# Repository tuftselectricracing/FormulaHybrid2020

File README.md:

# Formula Hybrid 2020
Files and such for Formula Hybrid 2020

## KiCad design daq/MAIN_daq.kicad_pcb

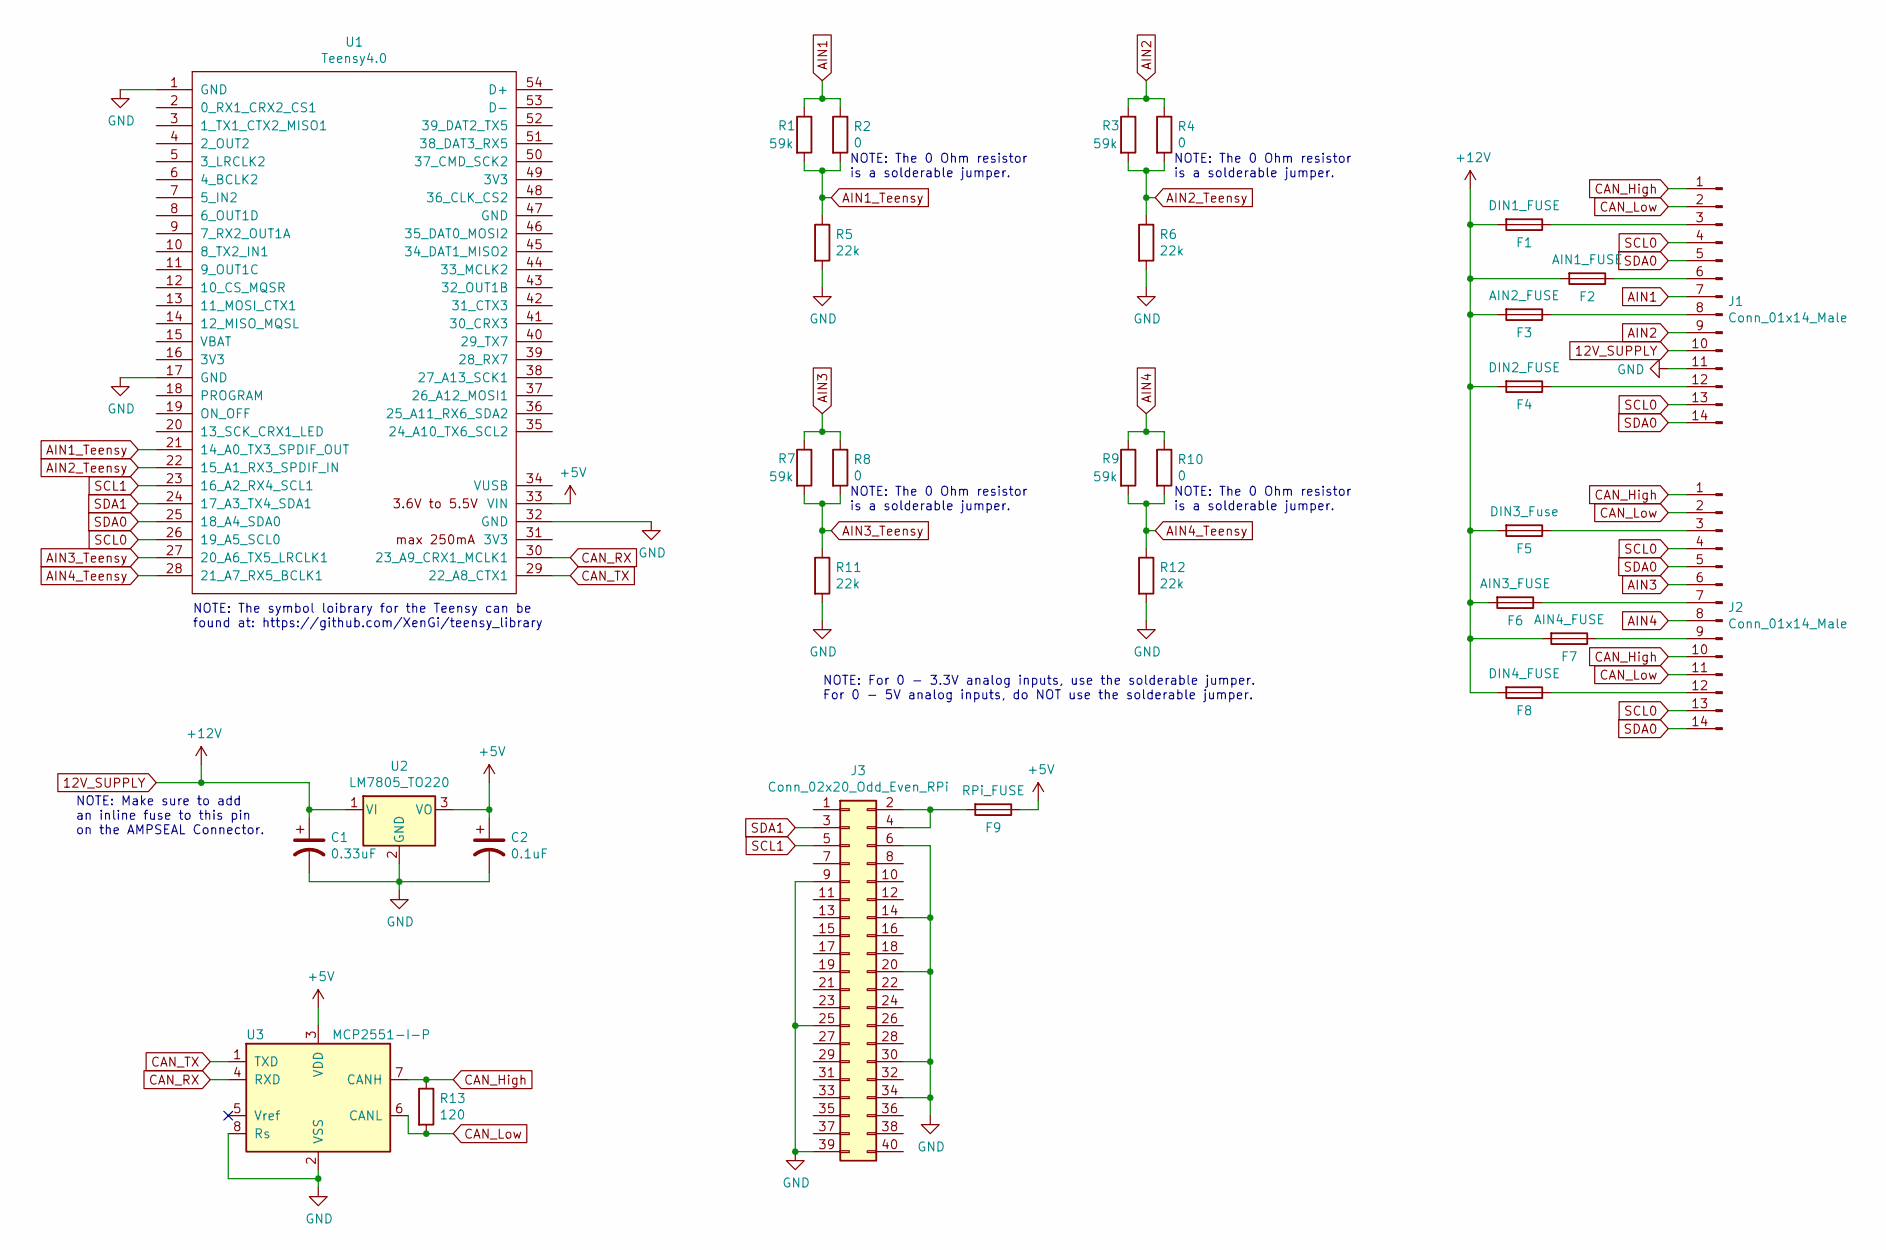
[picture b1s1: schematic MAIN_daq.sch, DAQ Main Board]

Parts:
C1: 0.33uF; C_0603_1608Metric_Pad1.08x0.95mm_HandSolder
C2: 0.1uF; C_0402_1005Metric_Pad0.74x0.62mm_HandSolder
F1: DIN1_FUSE; Fuseholder_Blade_Mini_Keystone_3568
F2: AIN1_FUSE; Fuseholder_Blade_Mini_Keystone_3568
F3: AIN2_FUSE; Fuseholder_Blade_Mini_Keystone_3568
F4: DIN2_FUSE; Fuseholder_Blade_Mini_Keystone_3568
F5: DIN3_Fuse; Fuseholder_Blade_Mini_Keystone_3568
F6: AIN3_FUSE; Fuseholder_Blade_Mini_Keystone_3568
F7: AIN4_FUSE; Fuseholder_Blade_Mini_Keystone_3568
F8: DIN4_FUSE; Fuseholder_Blade_Mini_Keystone_3568
F9: RPi_FUSE; Fuseholder_Blade_Mini_Keystone_3568
J1, J2: Conn_01x14_Male; TE_776266-1
J3: Conn_02x20_Odd_Even_RPi; PinHeader_2x20_P2.54mm_Vertical
R1, R3, R7, R9: 59k; R_0603_1608Metric_Pad0.98x0.95mm_HandSolder
R2, R4, R8, R10: 0; SolderJumper-2_P1.3mm_Open_TrianglePad1.0x1.5mm
R5, R6, R11, R12: 22k; R_0603_1608Metric_Pad0.98x0.95mm_HandSolder
R13: 120; R_0603_1608Metric_Pad0.98x0.95mm_HandSolder
U1: Teensy4.0; Teensy40
U2: LM7805_TO220; TO-220-3_Horizontal_TabDown
U3: MCP2551-I-P; DIP-8_W7.62mm

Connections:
12V_SUPPLY: C1.1, F1.2, F2.2, F3.2, F4.2, F5.2, F6.2, F7.2, F8.2, J1.10, U2.1 (VI)
+5V: C2.1, F9.1, U1.33 (VIN), U2.3 (VO), U3.3 (VDD)
AIN1: J1.7, R1.1, R2.1
AIN1_Teensy: R1.2, R2.2, R5.1, U1.21 (14_A0_TX3_SPDIF_OUT)
AIN2: J1.9, R3.1, R4.1
AIN2_Teensy: R3.2, R4.2, R6.1, U1.22 (15_A1_RX3_SPDIF_IN)
AIN3: J2.6, R7.1, R8.1
AIN3_Teensy: R7.2, R8.2, R11.1, U1.27 (20_A6_TX5_LRCLK1)
AIN4: J2.8, R9.1, R10.1
AIN4_Teensy: R9.2, R10.2, R12.1, U1.28 (21_A7_RX5_BCLK1)
CAN_High: J1.1, J2.1, J2.10, R13.1, U3.7 (CANH)
CAN_Low: J1.2, J2.2, J2.11, R13.2, U3.6 (CANL)
CAN_RX: U1.30 (23_A9_CRX1_MCLK1), U3.4 (RXD)
CAN_TX: U1.29 (22_A8_CTX1), U3.1 (TXD)
GND: C1.2, C2.2, J1.11, J3.6, J3.9, J3.14, J3.20, J3.25, J3.30, J3.34, J3.39, R5.2, R6.2, R11.2, R12.2, U1.1 (GND), U1.17 (GND), U1.32 (GND), U2.2 (GND), U3.2 (VSS), U3.8 (Rs)
unnamed: F1.1, J1.3
unnamed: F2.1, J1.6
unnamed: F3.1, J1.8
unnamed: F4.1, J1.12
unnamed: F5.1, J2.3
unnamed: F6.1, J2.7
unnamed: F7.1, J2.9
unnamed: F8.1, J2.12
unnamed: F9.2, J3.2, J3.4
SCL0: J1.4, J1.13, J2.4, J2.13, U1.26 (19_A5_SCL0)
SCL1: J3.5, U1.23 (16_A2_RX4_SCL1)
SDA0: J1.5, J1.14, J2.5, J2.14, U1.25 (18_A4_SDA0)
SDA1: J3.3, U1.24 (17_A3_TX4_SDA1)

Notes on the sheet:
NOTE: The symbol loibrary for the Teensy can be found at: https://github.com/XenGi/teensy_library
NOTE: The 0 Ohm resistor is a solderable jumper.
NOTE: Make sure to add an inline fuse to this pin on the AMPSEAL Connector.
NOTE: For 0 - 3.3V analog inputs, use the solderable jumper. For 0 - 5V analog inputs, do NOT use the solderable jumper.

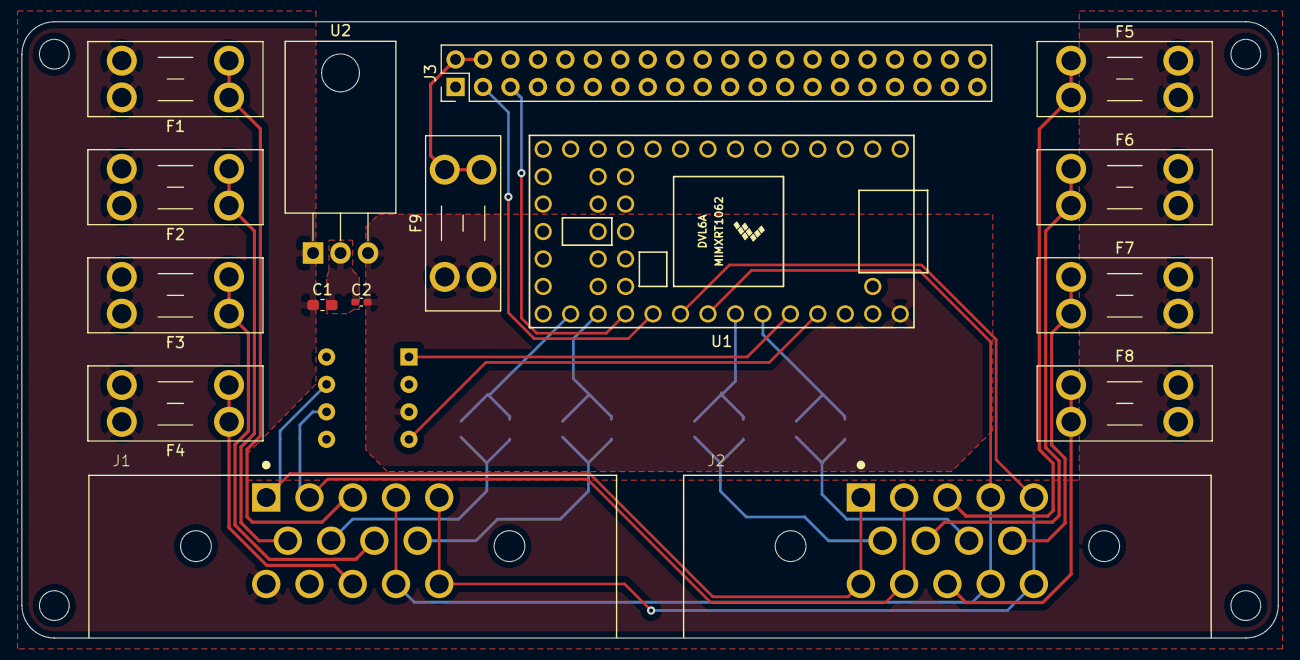
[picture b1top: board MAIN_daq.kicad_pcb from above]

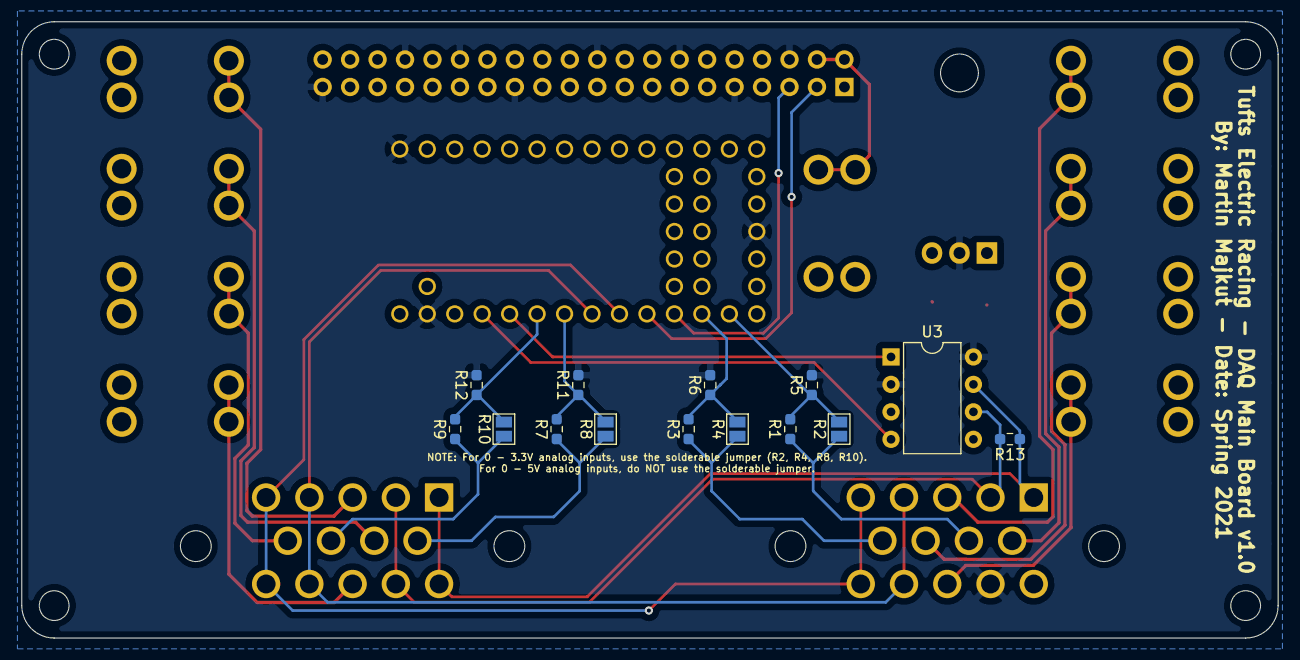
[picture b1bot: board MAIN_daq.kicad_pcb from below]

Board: 2 copper layers, 116.2 x 57.0 mm, 30 parts (14 on the bottom side), 28 nets.

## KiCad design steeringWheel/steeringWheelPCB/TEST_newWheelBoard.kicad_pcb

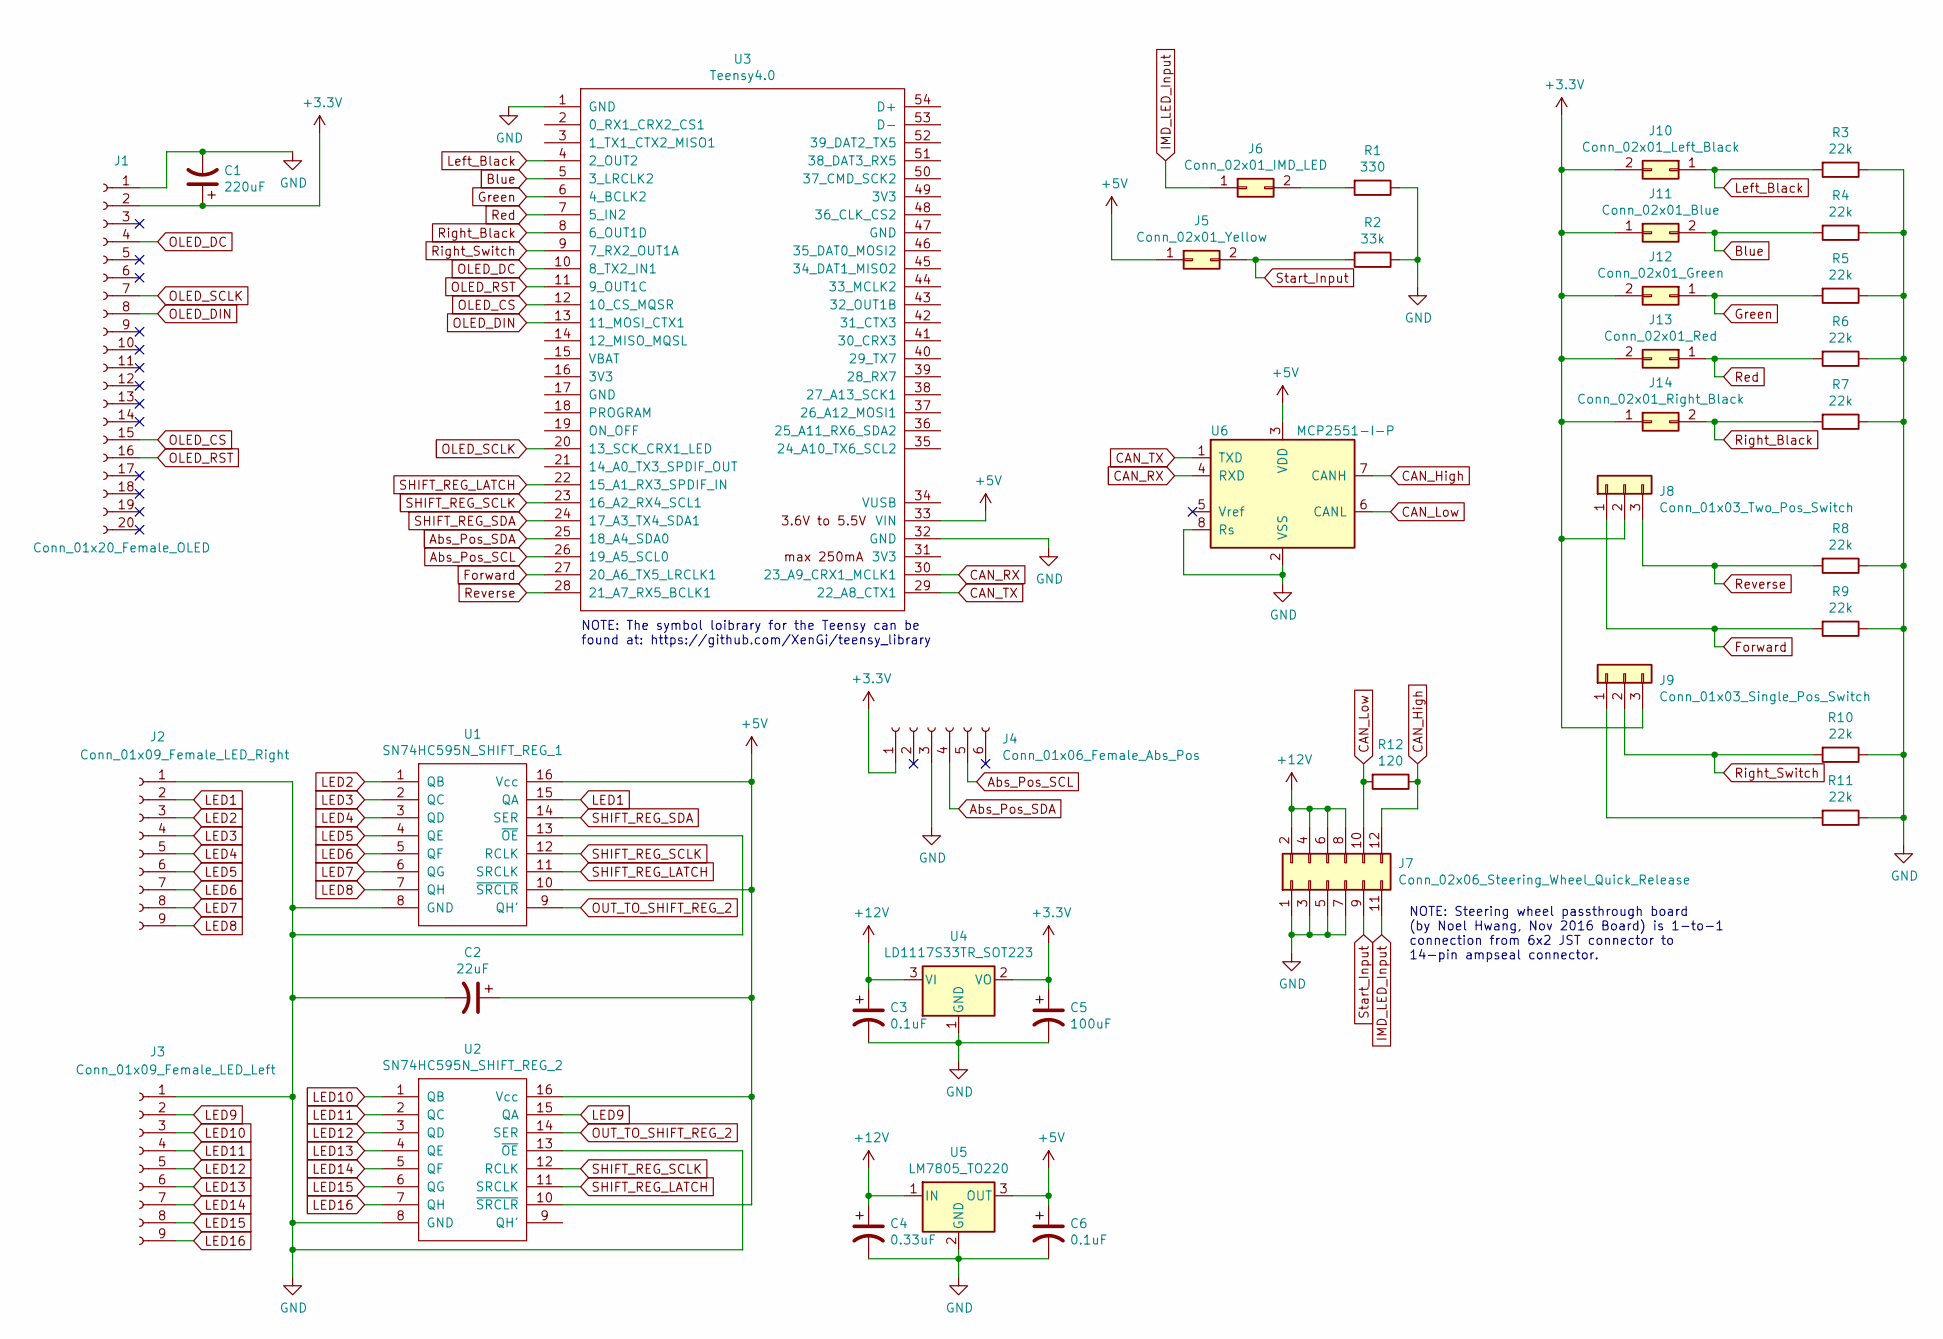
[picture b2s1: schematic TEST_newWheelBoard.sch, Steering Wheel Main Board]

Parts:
C1: 220uF; CP_Radial_D5.0mm_P2.00mm
C2: 22uF; CP_Radial_D4.0mm_P1.50mm
C3, C6: 0.1uF; C_0402_1005Metric
C4: 0.33uF; C_0603_1608Metric_Pad1.05x0.95mm_HandSolder
C5: 100uF; C_1206_3216Metric_Pad1.42x1.75mm_HandSolder
J1: Conn_01x20_Female_OLED; PinHeader_1x20_P2.54mm_Vertical
J2: Conn_01x09_Female_LED_Right; JST_PH_B9B-PH-K_1x09_P2.00mm_Vertical
J3: Conn_01x09_Female_LED_Left; JST_PH_B9B-PH-K_1x09_P2.00mm_Vertical
J4: Conn_01x06_Female_Abs_Pos; PinHeader_1x06_P2.54mm_Vertical
J5: Conn_02x01_Yellow; JST_PH_B2B-PH-K_1x02_P2.00mm_Vertical
J6: Conn_02x01_IMD_LED; JST_PH_B2B-PH-K_1x02_P2.00mm_Vertical
J7: Conn_02x06_Steering_Wheel_Quick_Release; JST_PHD_S12B-PHDSS_2x06_P2.00mm_Horizontal
J8: Conn_01x03_Two_Pos_Switch; JST_PH_B3B-PH-K_1x03_P2.00mm_Vertical
J9: Conn_01x03_Single_Pos_Switch; JST_PH_B3B-PH-K_1x03_P2.00mm_Vertical
J10: Conn_02x01_Left_Black; JST_PH_B2B-PH-K_1x02_P2.00mm_Vertical
J11: Conn_02x01_Blue; JST_PH_B2B-PH-K_1x02_P2.00mm_Vertical
J12: Conn_02x01_Green; JST_PH_B2B-PH-K_1x02_P2.00mm_Vertical
J13: Conn_02x01_Red; JST_PH_B2B-PH-K_1x02_P2.00mm_Vertical
J14: Conn_02x01_Right_Black; JST_PH_B2B-PH-K_1x02_P2.00mm_Vertical
R1: 330; R_0402_1005Metric
R2: 33k; R_0603_1608Metric_Pad1.05x0.95mm_HandSolder
R3, R4, R5, R6, R7, R8, R9, R10, R11: 22k; R_0603_1608Metric_Pad1.05x0.95mm_HandSolder
R12: 120; R_0603_1608Metric_Pad1.05x0.95mm_HandSolder
U1: SN74HC595N_SHIFT_REG_1; DIP-16_W7.62mm_Socket
U2: SN74HC595N_SHIFT_REG_2; DIP-16_W7.62mm_Socket
U3: Teensy4.0; Teensy40
U4: LD1117S33TR_SOT223; TO-220-3_Horizontal_TabDown
U5: LM7805_TO220; TO-220-3_Horizontal_TabDown
U6: MCP2551-I-P; DIP-8_W7.62mm

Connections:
+3V3: C1.1, C5.1, J1.2, J4.1, J8.2, J9.3, J10.2, J11.1, J12.2, J13.2, J14.1, U4.2 (VO)
+5V: C2.1, C6.1, J5.1, U1.10 (~SRCLR), U1.16 (Vcc), U2.10 (~SRCLR), U2.16 (Vcc), U3.33 (VIN), U5.3 (OUT), U6.3 (VDD)
+12V: C3.1, C4.1, J7.2, J7.4, J7.6, J7.8, U4.3 (VI), U5.1 (IN)
Abs_Pos_SCL: J4.5, U3.26 (19_A5_SCL0)
Abs_Pos_SDA: J4.4, U3.25 (18_A4_SDA0)
Blue: J11.2, R4.2, U3.5 (3_LRCLK2)
CAN_High: J7.12, R12.1, U6.7 (CANH)
CAN_Low: J7.10, R12.2, U6.6 (CANL)
CAN_RX: U3.30 (23_A9_CRX1_MCLK1), U6.4 (RXD)
CAN_TX: U3.29 (22_A8_CTX1), U6.1 (TXD)
Forward: J8.1, R9.2, U3.27 (20_A6_TX5_LRCLK1)
GND: C1.2, C2.2, C3.2, C4.2, C5.2, C6.2, J1.1, J2.1, J3.1, J4.3, J7.1, J7.3, J7.5, J7.7, R1.1, R2.1, R3.1, R4.1, R5.1, R6.1, R7.1, R8.1, R9.1, R10.1, R11.1, U1.8 (GND), U1.13 (~OE), U2.8 (GND), U2.13 (~OE), U3.1 (GND), U3.32 (GND), U4.1 (GND), U5.2 (GND), U6.2 (VSS), U6.8 (Rs)
Green: J12.1, R5.2, U3.6 (4_BCLK2)
IMD_LED_Input: J6.1, J7.11
LED1: J2.2, U1.15 (QA)
LED2: J2.3, U1.1 (QB)
LED3: J2.4, U1.2 (QC)
LED4: J2.5, U1.3 (QD)
LED5: J2.6, U1.4 (QE)
LED6: J2.7, U1.5 (QF)
LED7: J2.8, U1.6 (QG)
LED8: J2.9, U1.7 (QH)
LED9: J3.2, U2.15 (QA)
LED10: J3.3, U2.1 (QB)
LED11: J3.4, U2.2 (QC)
LED12: J3.5, U2.3 (QD)
LED13: J3.6, U2.4 (QE)
LED14: J3.7, U2.5 (QF)
LED15: J3.8, U2.6 (QG)
LED16: J3.9, U2.7 (QH)
Left_Black: J10.1, R3.2, U3.4 (2_OUT2)
unnamed: J6.2, R1.2
unnamed: J9.1, R11.2
OLED_CS: J1.15, U3.12 (10_CS_MQSR)
OLED_DC: J1.4, U3.10 (8_TX2_IN1)
OLED_DIN: J1.8, U3.13 (11_MOSI_CTX1)
OLED_RST: J1.16, U3.11 (9_OUT1C)
OLED_SCLK: J1.7, U3.20 (13_SCK_CRX1_LED)
OUT_TO_SHIFT_REG_2: U1.9 (QH'), U2.14 (SER)
Red: J13.1, R6.2, U3.7 (5_IN2)
Reverse: J8.3, R8.2, U3.28 (21_A7_RX5_BCLK1)
Right_Black: J14.2, R7.2, U3.8 (6_OUT1D)
Right_Switch: J9.2, R10.2, U3.9 (7_RX2_OUT1A)
SHIFT_REG_LATCH: U1.11 (SRCLK), U2.11 (SRCLK), U3.22 (15_A1_RX3_SPDIF_IN)
SHIFT_REG_SCLK: U1.12 (RCLK), U2.12 (RCLK), U3.23 (16_A2_RX4_SCL1)
SHIFT_REG_SDA: U1.14 (SER), U3.24 (17_A3_TX4_SDA1)
Start_Input: J5.2, J7.9, R2.2

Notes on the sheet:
NOTE: Steering wheel passthrough board (by Noel Hwang, Nov 2016 Board) is 1-to-1 connection from 6x2 JST connector to 14-pin ampseal connector.
NOTE: The symbol loibrary for the Teensy can be found at: https://github.com/XenGi/teensy_library

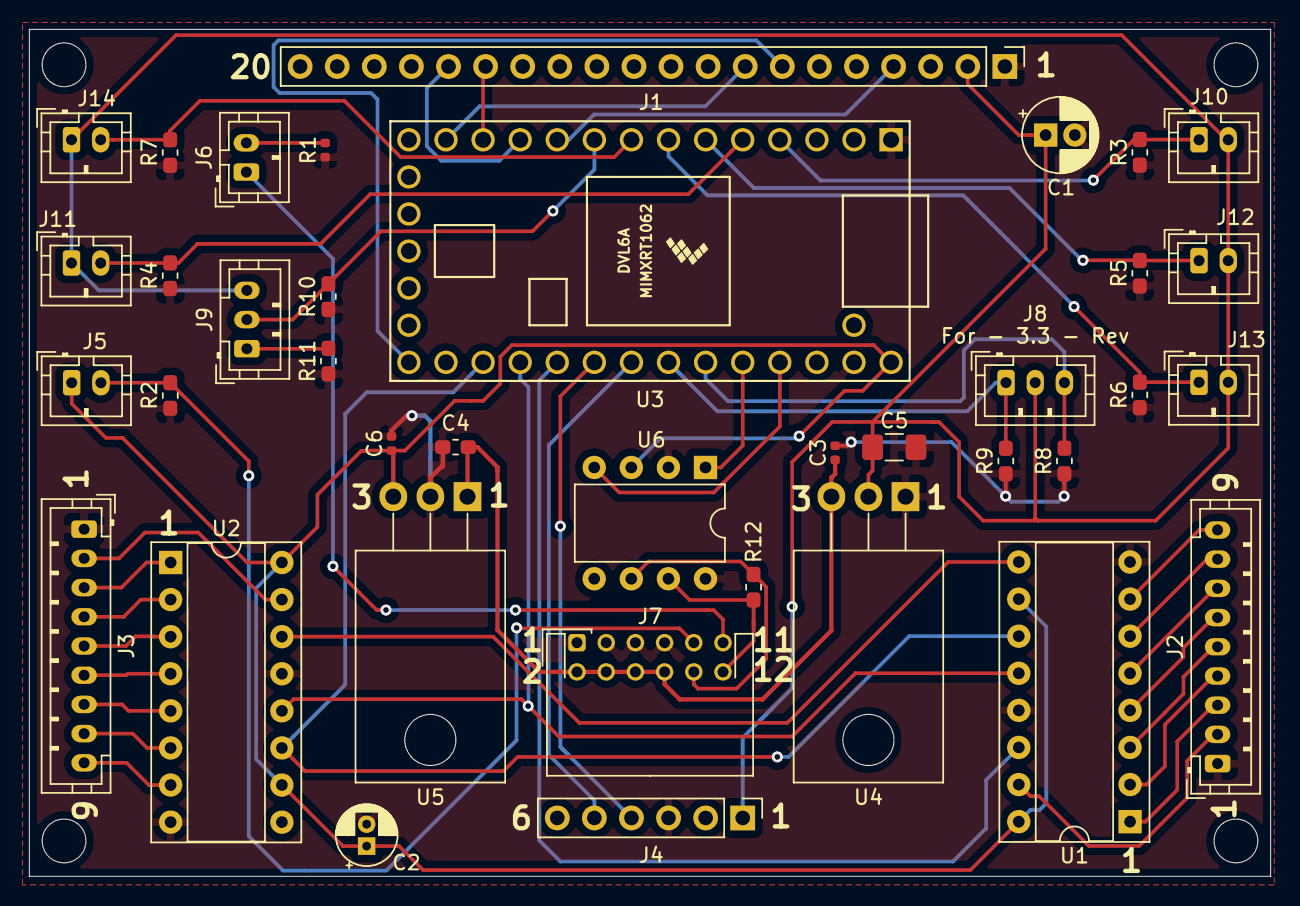
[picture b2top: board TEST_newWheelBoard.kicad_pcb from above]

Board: 2 copper layers, 85.0 x 58.0 mm, 38 parts (0 on the bottom side), 47 nets.

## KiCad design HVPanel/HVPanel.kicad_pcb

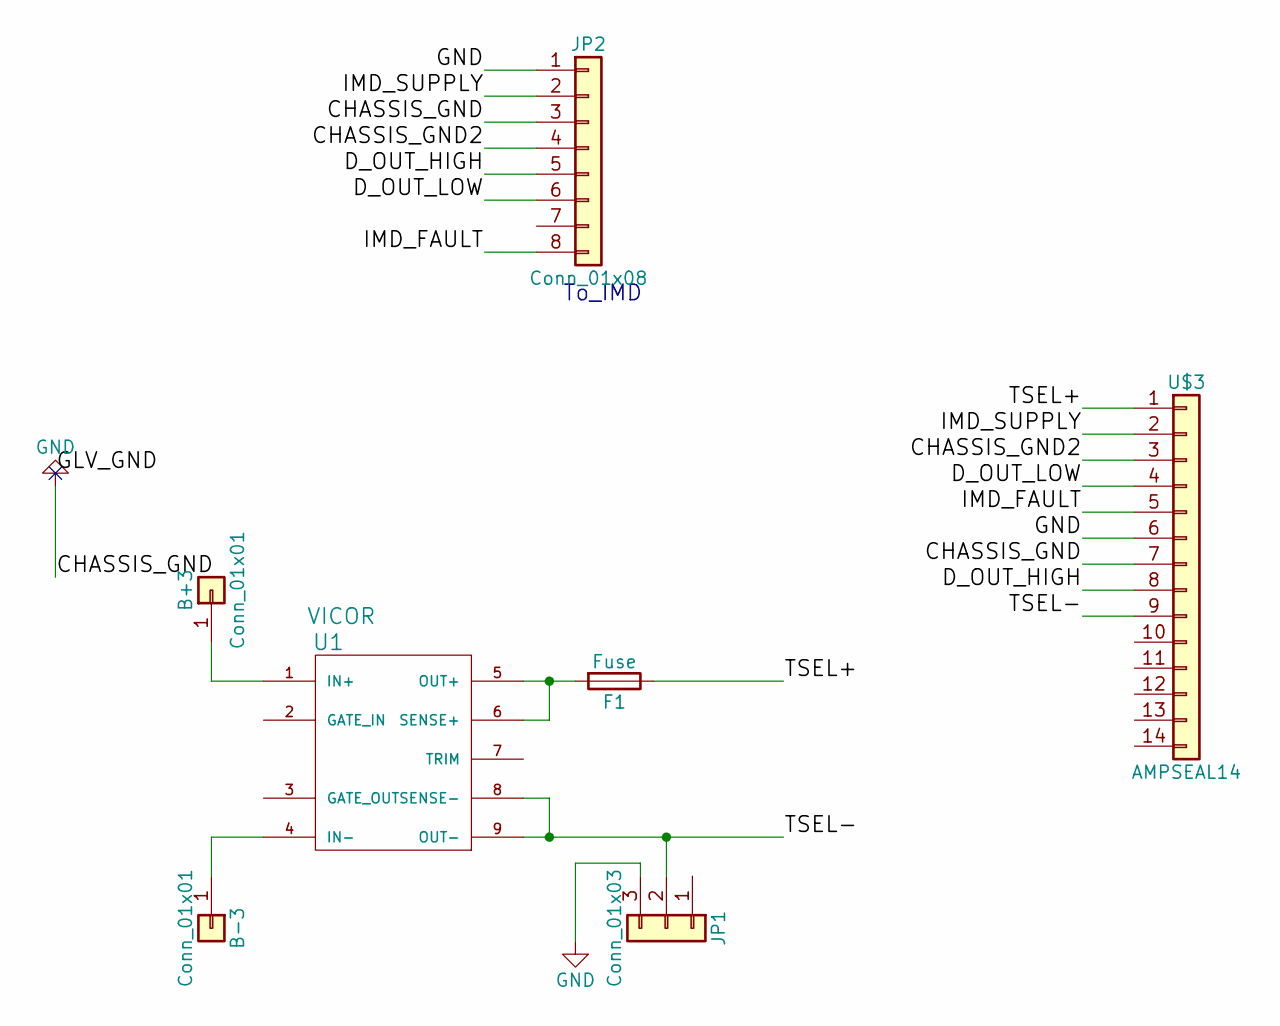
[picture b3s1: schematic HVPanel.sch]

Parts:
B+3: Conn_01x01; SolderWirePad_single_1-5mmDrill
B-3: Conn_01x01; SolderWirePad_single_1-5mmDrill
F1: Fuse; BladeFuse-Mini_Keystone_3568
JP1: Conn_01x03; Pin_Header_Straight_1x03_Pitch2.54mm
JP2: Conn_01x08; Pin_Header_Straight_1x08_Pitch2.54mm
U1: VICOR
U$3: AMPSEAL14; AMP14

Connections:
/CHASSIS_GND2: JP2.4, U$3.3
/D_OUT_HIGH: JP2.5, U$3.8
/D_OUT_LOW: JP2.6, U$3.4
/IMD_FAULT: JP2.8, U$3.5
/IMD_SUPPLY: JP2.2, U$3.2
/TSEL+: F1.1, U$3.1
/TSEL-: JP1.2, U1.8 (SENSE-), U1.9 (OUT-), U$3.9
GND: JP1.3, JP2.1, JP2.3, U$3.6, U$3.7
unnamed: B+3.1, U1.1 (IN+)
unnamed: B-3.1, U1.4 (IN-)
unnamed: F1.2, U1.5 (OUT+), U1.6 (SENSE+)

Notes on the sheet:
To_IMD

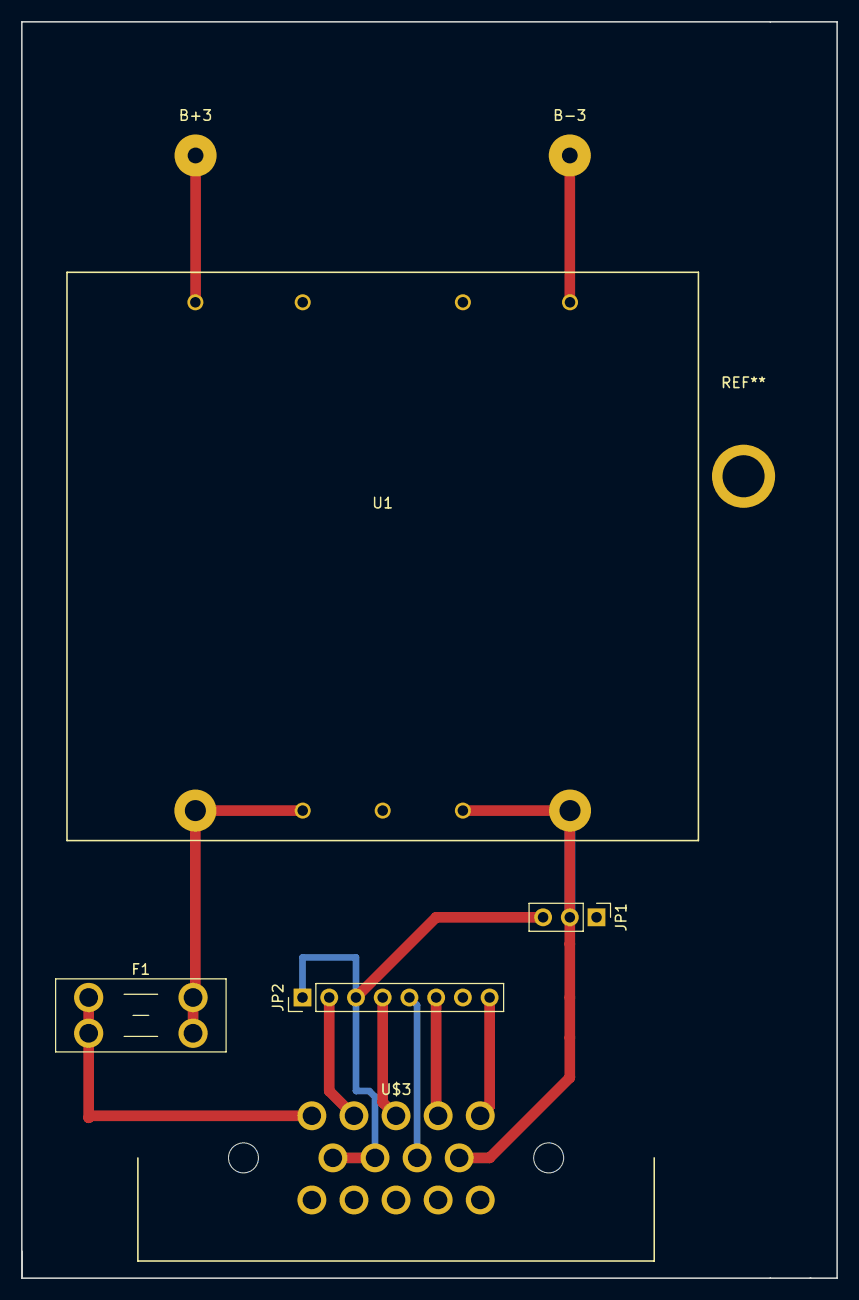
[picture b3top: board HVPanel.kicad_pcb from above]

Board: 2 copper layers, 77.5 x 119.4 mm, 7 parts (0 on the bottom side), 11 nets.

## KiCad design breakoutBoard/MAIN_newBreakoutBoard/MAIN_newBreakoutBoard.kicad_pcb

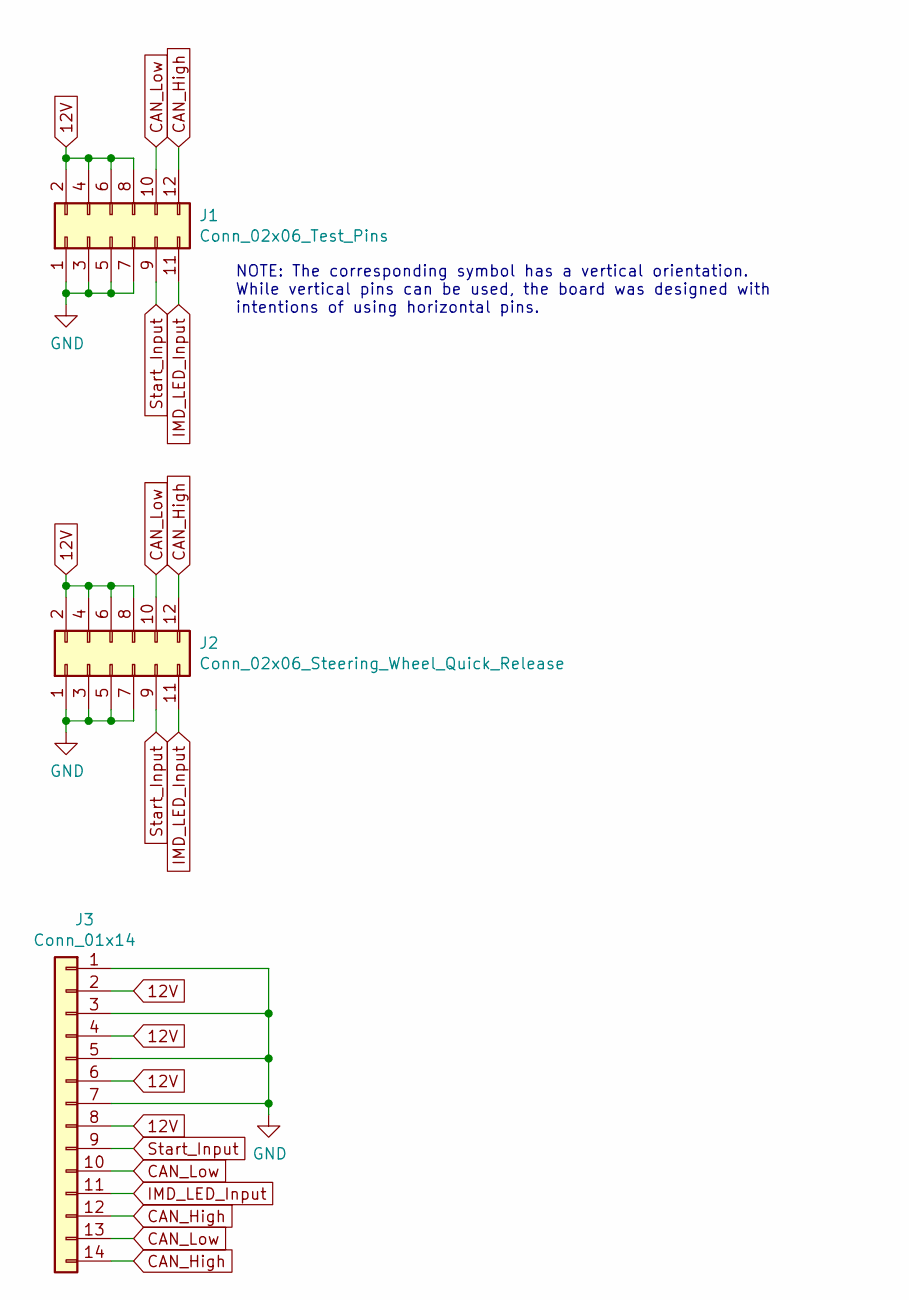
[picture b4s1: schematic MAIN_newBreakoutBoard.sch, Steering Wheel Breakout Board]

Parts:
J1: Conn_02x06_Test_Pins; PinSocket_2x06_P2.54mm_Vertical
J2: Conn_02x06_Steering_Wheel_Quick_Release; JST_PHD_S12B-PHDSS_2x06_P2.00mm_Horizontal
J3: Conn_01x14; TE_776266-1

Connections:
12V: J1.2, J1.4, J1.6, J1.8, J2.2, J2.4, J2.6, J2.8, J3.2, J3.4, J3.6, J3.8
CAN_High: J1.12, J2.12, J3.12, J3.14
CAN_Low: J1.10, J2.10, J3.10, J3.13
GND: J1.1, J1.3, J1.5, J1.7, J2.1, J2.3, J2.5, J2.7, J3.1, J3.3, J3.5, J3.7
IMD_LED_Input: J1.11, J2.11, J3.11
Start_Input: J1.9, J2.9, J3.9

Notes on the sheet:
NOTE: The corresponding symbol has a vertical orientation. While vertical pins can be used, the board was designed with intentions of using horizontal pins.

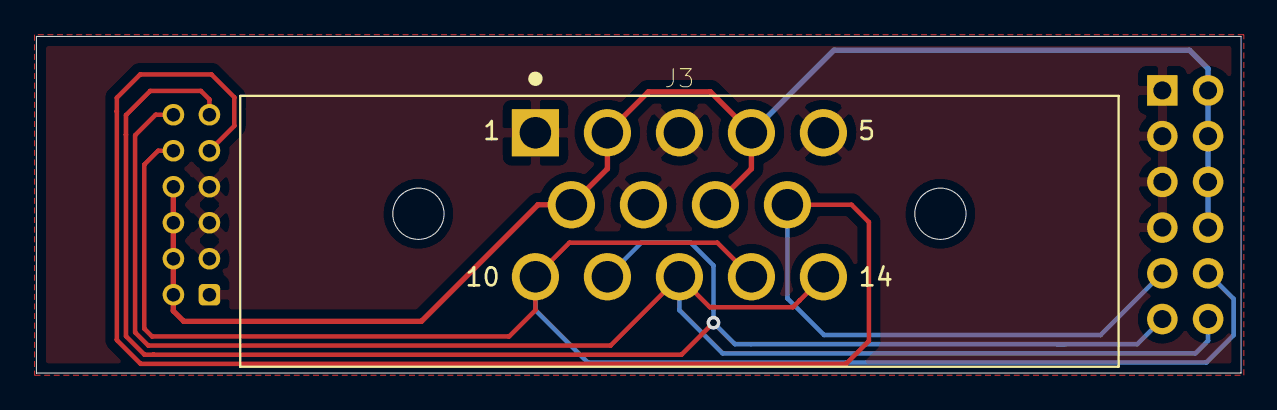
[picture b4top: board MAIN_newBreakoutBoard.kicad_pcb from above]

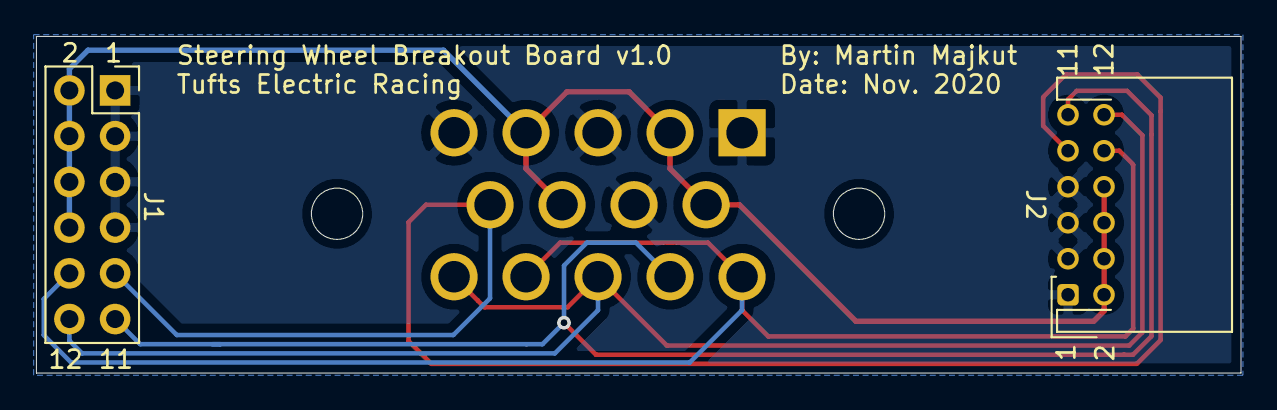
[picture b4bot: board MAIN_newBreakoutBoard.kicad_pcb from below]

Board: 2 copper layers, 66.9 x 18.7 mm, 3 parts (2 on the bottom side), 6 nets.

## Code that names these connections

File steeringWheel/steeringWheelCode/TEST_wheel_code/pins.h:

/*
	pins.h

	This is the supplimentary header file to wheel_code.ino file. It defines
	all the pins used by the Teensy 4.0. The pins are defined as macros to 
	minimize the storage used by the code, thus allowing the board to run
	as quickly as possible. The names used are the same names in the 
	schematic for the board.

	By:   Martin Majkut
			  Tufts Electric Racing
	Date: Aug. 3, 2020
*/

#ifndef PINS_H
#define PINS_H

// Pins for the OLED display (link: https://www.adafruit.com/product/2674)
#define OLED_SCLK 13
#define OLED_DIN 11
#define OLED_CS 10
#define OLED_RST 9
#define OLED_DC 8

// Pins for reading buttons and switches
// (Note: start input button, the yellow button at the time of writing this 
// documentation, bipasses the Teensy and inputs to the motherboard, which 
// why it is not read by the steering wheel)
#define LEFT_BLACK 2
#define BLUE 3
#define GREEN 4
#define RED 5
#define RIGHT_BLACK 6
#define RIGHT_SWITCH 7
#define FORWARD 20
#define REVERSE 21

// Pins for communicating to shift registers thus turning on LEDs
// (link to shift register: https://www.ti.com/store/ti/en/p/product/?p=SN74HC595N)
// NOTE: SCLK and LATCH pins are reversed in schematic (Jan. 2020 Board); will
//       need to be updated in future iterations of board
#define SHIFT_REG_LATCH 16
#define SHIFT_REG_SCLK 15
#define SHIFT_REG_SDA 17

// Pins for absolute position sensor (link: https://www.adafruit.com/product/2472)
#define Abs_Pos_SDA 18
#define Abs_Pos_SCL 19

#endif

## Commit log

2020-08-09 Created folder for steering wheel files
2020-08-09 Created folder for KiCad files
2020-08-09 Created .gitignore before first commit of files
2020-08-09 Added KiCad project
    These files are up to date and are currently the ones being used in the race car's steering wheel as of 8/9/2020.
2020-08-09 Add PCB testing code
2020-08-12 Updated testing code
    Turns out the display wasn't printing what I wanted it to print because I forgot to add in the command that updates the display
2020-08-14 Updated testing code
    The code now responds in real time letting the user know if a button is being read correctly
2020-08-20 Another update to testing code
    Now the code connects to the absolute position sensor and reads position of the steering wheel and displays it on the screen
2020-09-04 LED testing added to testing code + light reformatting
    You know, it becomes really difficult to test something when pins on a board are reversed. Notes added to steering wheel board and code reflect changes that need to implemented for the next iteration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
2020-09-20 CAN bus testing code added
    Code for a swecond Teensy was added to test and verify CAN communication with the steering wheel. The code on the steering wheel was also updated to display CAN messages
2020-11-14 Added breakout board KiCad project
    This is the project for the breakout board that allows the steering wheel to connect to the rest of the race car.
2020-11-15 Slight design updates and gerbers created
    I created gerbers even though OSH Park does not require gerber files.... But whatever, wanted to get some more experience using KiCad :)
2020-11-24 Made use of entire ampseal connector
    Had a late night ah ha momment;; Figured I would make use of all the pins on the ampseal connect and make it so we have the option to add another CAN node at the front of the car if need be.
2020-11-24 Forgot to generate updated gerbers after updating pcb
2021-04-15 Found design files from previous years to save to the archive
2021-04-16 Updated archive files to open in KiCAD 5.x
    NOTE: The PCB may not update correctly. However, since these files are only used as reference and the PCB file will open up and looks correct, only the schematic was updated.
2022-01-24 Uploading daq KiCad Project
    I forgot I generated these files awhile ago (no one from the team bugged me about them, which is a little concerning). Uploading after opening to verify files were complete.
2022-01-24 Uploaded DAQ KiCad Project
    After my initial upload of these files, I realized that some of the files were not like I left them in May 2021 (just some text on the silk screen layers was missing. Couldn't find any backups so re-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
